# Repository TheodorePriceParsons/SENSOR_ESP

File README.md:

# Robot Summer

Sensor board firmware and PCB for our ENPH 253 (UBC Engineering Physics, summer 2026) competition robot. An ESP32-S3 detects the 1 kHz and 10 kHz IR beacons, measures two metal-detector oscillators to find aluminium in rocks, and streams the results to the main ESP over UART.

<table> <tr> <td align="center" width="50%"></td> <td align="center" width="50%"></td> </tr> <tr> <td align="center"><sub>Mecanum drive base with the gripper arm and one metal-detector coil</sub></td> <td align="center"><sub>Front view: both detector coils, power and beacon-select switches</sub></td> </tr> </table>

## Sensor board

- **IR front end:** QSD124 phototransistor, an op-amp buffer providing a 2.5 V virtual ground, and a non-inverting band-pass stage (gain 4, about 160 Hz to 48 kHz), divided down into the ESP32's ADC range.
- **Metal detectors:** two 2N3904 Colpitts oscillators; the coils connect through screw terminals.
- **Connectors:** 5 V power and UART to the main board on JST-PH.
- **Layout:** metal detectors, ESP32 and IR chain sit in separate areas over a solid bottom ground pour, with bulk and local decoupling on the 5 V rail.
- 2-layer, all through-hole.

## Firmware

### IR beacon detection

The phototransistor signal is sampled at a fixed, hardware-clocked 50 kHz using the ADC continuous (DMA) driver. Samples are grouped into non-overlapping blocks of 500 (10 ms), the mean is removed, and two Goertzel filters measure the amplitude at 1 kHz and 10 kHz. The block size puts both tones on exact DFT bins (k = 10 and k = 100), so neither leaks into neighbouring bins. Each tone has its own threshold, since the analog band-pass does not have flat gain.

### Metal detection

Each detector is a Colpitts LC oscillator (~150 kHz). Metal near the coil shifts its frequency. One PCNT unit per detector counts rising edges in hardware; every 1.5 s the firmware divides the count by the elapsed time measured with `esp_timer`, giving about 0.7 Hz resolution. The main ESP compares against a baseline and decides whether metal is present.

### Build

```sh
idf.py set-target esp32s3
idf.py build flash monitor
```

## Mechanical mounts

<table>
  <tr>
    <td align="center" width="33%"></td>
    <td align="center" width="33%"></td>
    <td align="center" width="33%"></td>
  </tr>
  <tr>
    <td align="center"><sub>Metal detector coil mount</sub></td>
    <td align="center"><sub>Mount bracket</sub></td>
    <td align="center"><sub>Rock basket</sub></td>
  </tr>
</table>

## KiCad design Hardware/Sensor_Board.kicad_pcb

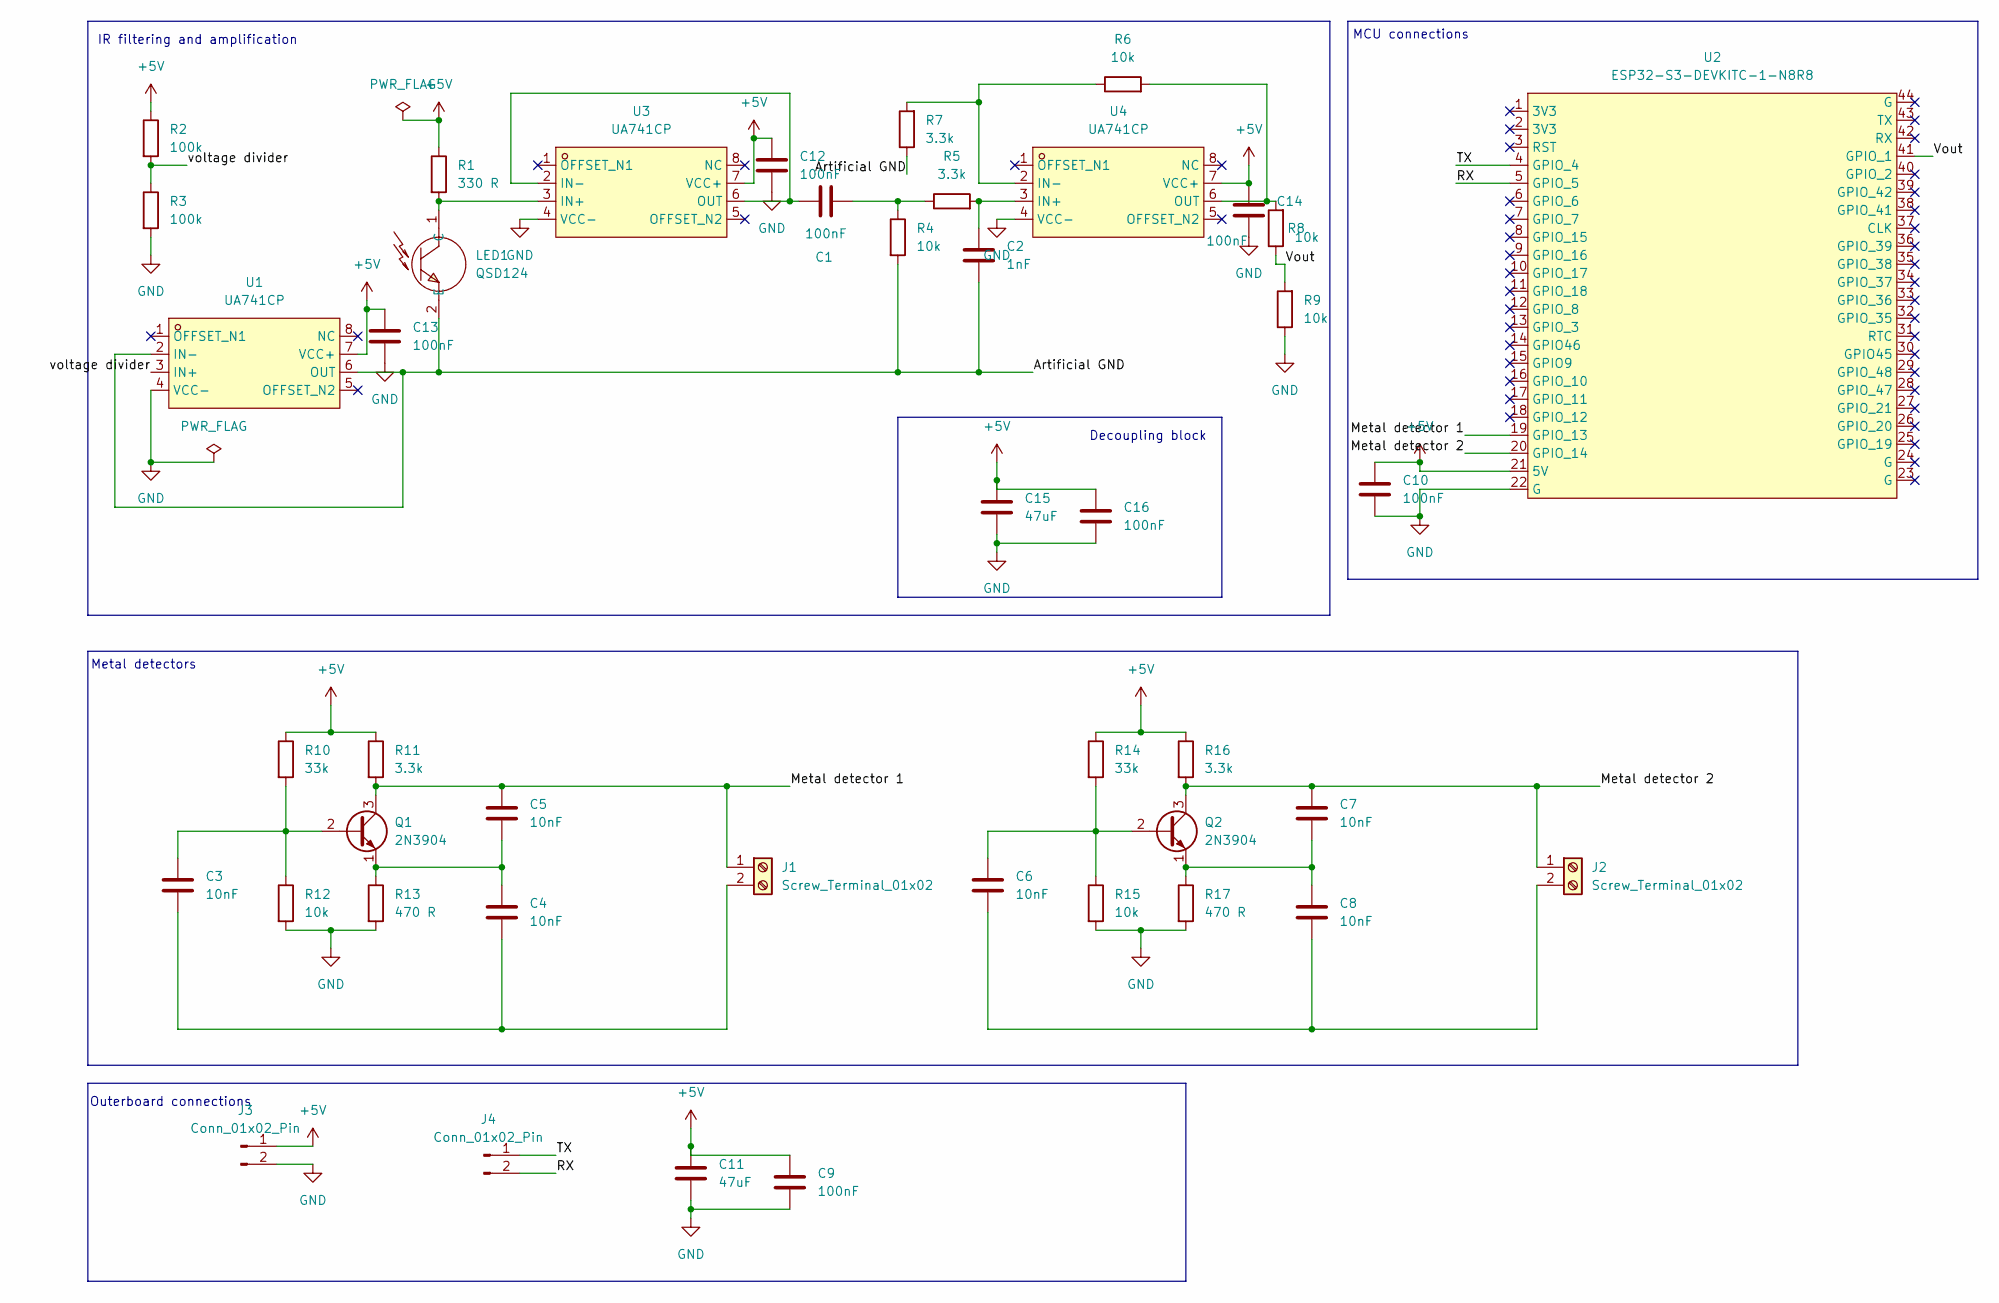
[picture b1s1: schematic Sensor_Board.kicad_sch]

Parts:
C1, C9, C10, C12, C13, C14, C16: 100nF; C_Disc_D5.0mm_W2.5mm_P2.50mm
C2: 1nF; C_Disc_D5.0mm_W2.5mm_P2.50mm
C3, C4, C5, C6, C7, C8: 10nF; C_Disc_D5.0mm_W2.5mm_P2.50mm
C11, C15: 47uF; C_Radial_D6.3mm_H5.0mm_P2.50mm
J1, J2: Screw_Terminal_01x02; TerminalBlock_Phoenix_MKDS-1,5-2_1x02_P5.00mm_Horizontal
J3, J4: Conn_01x02_Pin; JST_PH_B2B-PH-K_1x02_P2.00mm_Vertical
LED1: QSD124; LED-TH_BD5.0-P2.54-FD; MPN QSD124; LCSC ID C897963
Q1, Q2: 2N3904; TO-92_Inline
R1: 330 R; R_Axial_DIN0207_L6.3mm_D2.5mm_P7.62mm_Horizontal
R2, R3: 100k; R_Axial_DIN0207_L6.3mm_D2.5mm_P7.62mm_Horizontal
R4, R6, R8, R9, R12, R15: 10k; R_Axial_DIN0207_L6.3mm_D2.5mm_P7.62mm_Horizontal
R5, R7, R11, R16: 3.3k; R_Axial_DIN0207_L6.3mm_D2.5mm_P7.62mm_Horizontal
R10, R14: 33k; R_Axial_DIN0207_L6.3mm_D2.5mm_P7.62mm_Horizontal
R13, R17: 470 R; R_Axial_DIN0207_L6.3mm_D2.5mm_P7.62mm_Horizontal
U1, U3, U4: UA741CP; DIP-8_L9.6-W6.4-P2.54-LS7.6-BL-1; MPN UA741CP; LCSC ID C78758
U2: ESP32-S3-DEVKITC-1-N8R8; CONN-TH_ESP32-S3-DEVKITC-1U-N8; MPN ESP32-S3-DEVKITC-1-N8R8; LCSC ID C20541519

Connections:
+5V: C9.1, C10.1, C11.1, C12.1, C13.1, C14.1, C15.1, C16.1, J3.1, R1.1, R2.1, R10.1, R11.1, R14.1, R16.1, U1.7 (VCC+), U2.21 (5V), U3.7 (VCC+), U4.7 (VCC+)
/Artificial GND: C2.1, LED1.2 (E), R4.2, R7.1, U1.2 (IN-), U1.6 (OUT)
/Metal detector 1: C5.2, J1.1, Q1.3 (C), R11.2, U2.19 (GPIO_13)
/Metal detector 2: C7.2, J2.1, Q2.3 (C), R16.2, U2.20 (GPIO_14)
/RX: J4.2, U2.5 (GPIO_5)
/TX: J4.1, U2.4 (GPIO_4)
/Vout: R8.1, R9.2, U2.41 (GPIO_1)
/voltage divider: R2.2, R3.1, U1.3 (IN+)
GND: C9.2, C10.2, C11.2, C12.2, C13.2, C14.2, C15.2, C16.2, J3.2, R3.2, R9.1, R12.2, R13.2, R15.2, R17.2, U1.4 (VCC-), U2.22 (G), U3.4 (VCC-), U4.4 (VCC-)
unnamed: C1.2, R4.1, R5.1
unnamed: C3.2, C4.1, J1.2
unnamed: C6.2, C8.1, J2.2
unnamed: LED1.1 (C), R1.2, U3.3 (IN+)
unnamed: C3.1, Q1.2 (B), R10.2, R12.1
unnamed: C4.2, C5.1, Q1.1 (E), R13.1
unnamed: C6.1, Q2.2 (B), R14.2, R15.1
unnamed: C7.1, C8.2, Q2.1 (E), R17.1
unnamed: C1.1, U3.2 (IN-), U3.6 (OUT)
unnamed: C2.2, R5.2, U4.3 (IN+)
unnamed: R6.1, R7.2, U4.2 (IN-)
unnamed: R6.2, R8.2, U4.6 (OUT)

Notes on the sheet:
Metal detectors
IR filtering and amplification
Outerboard connections
MCU connections
Decoupling block

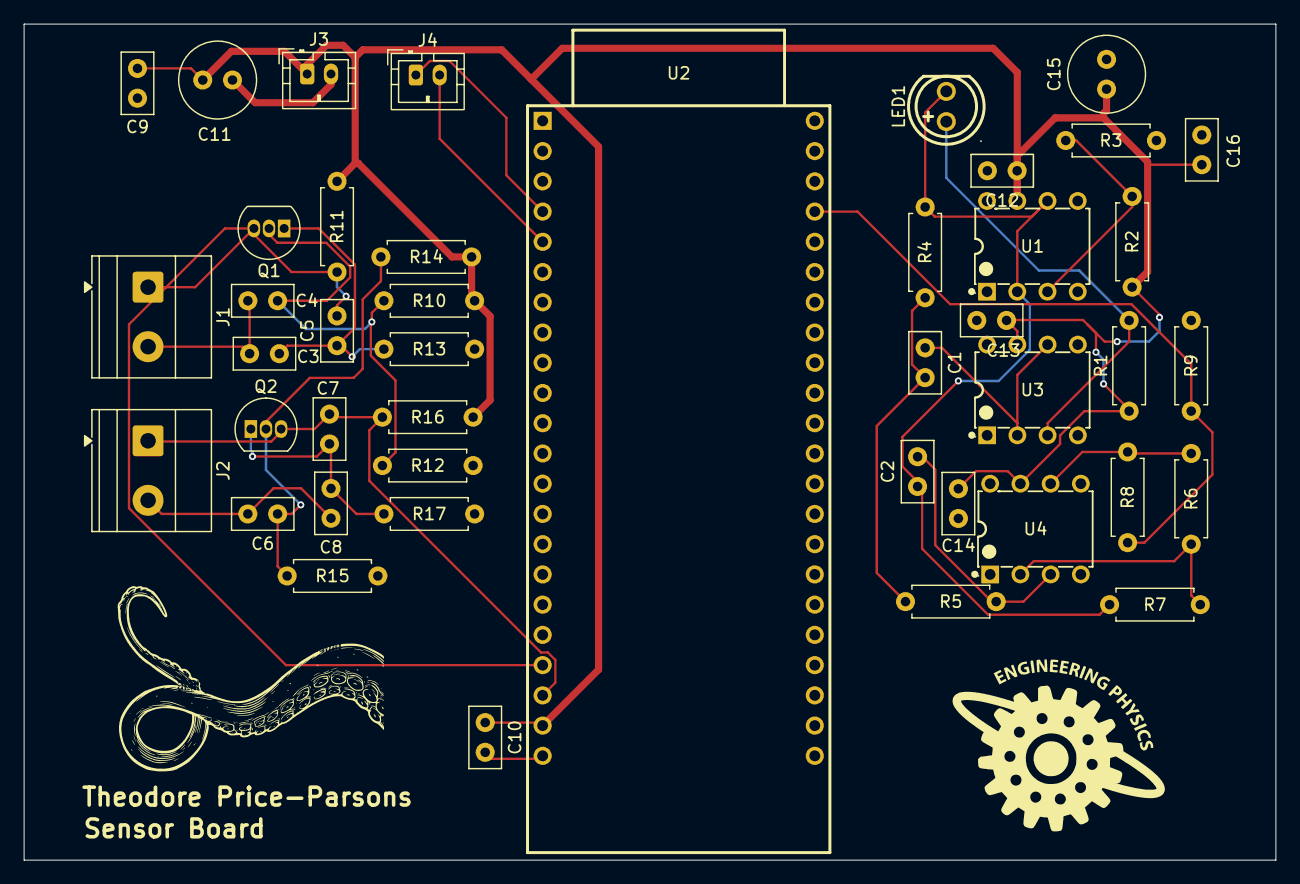
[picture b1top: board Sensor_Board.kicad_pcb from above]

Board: 2 copper layers, 105.2 x 70.2 mm, 44 parts (0 on the bottom side), 21 nets.
